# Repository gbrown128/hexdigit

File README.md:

# hexdigit
A 4-bit hex seven-segment display decoder.

Hex decoding by default, with blanking signal and an option to force decimal
display only.

Once the hardware is made, a range of additional features are planned, taking
advantage of the daisy chaining feature using UART.

# Hardware

The above render shows the basic goal of the product - to
fit entirley in the space of the seven-segment display, and
also have a DIP footprint for breadboarding.

The harware is based on an ATTiny1634, which has a whole 
host of capacity for future expansion.

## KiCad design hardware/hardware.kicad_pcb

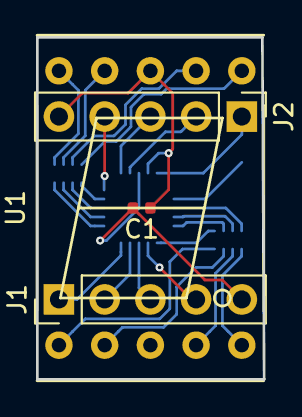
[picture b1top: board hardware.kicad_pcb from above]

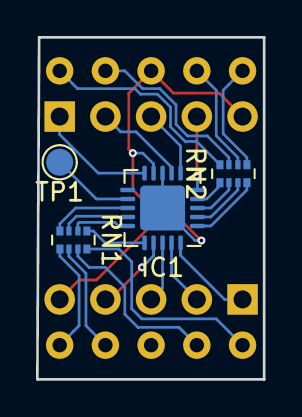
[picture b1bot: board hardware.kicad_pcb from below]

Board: 2 copper layers, 12.6 x 19.0 mm, 8 parts (4 on the bottom side), 27 nets.

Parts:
C1: 1u; C_0402_1005Metric
IC1: ATTINY1634-MU; QFN-20-1EP_4x4mm_P0.5mm_EP2.5x2.5mm
J1, J2: Conn_01x05_Male; PinHeader_1x05_P2.54mm_Vertical
RN1, RN2: 150; R_Array_Convex_4x0402
TP1: ~RESET; TestPoint_Pad_D1.5mm
U1: KCSA02-105; 7SegmentLED_LTS6760_LTS6780

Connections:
+5V: C1.1, IC1.9, J2.5, U1.8
/DA: RN2.7, U1.7
/DB: RN2.8, U1.6
/DC: RN1.6, U1.4
/DD: RN1.7, U1.2
/DDP: RN1.5, U1.5
/DE: RN1.8, U1.1
/DF: RN2.6, U1.9
/DG: RN2.5, U1.10
/~RESET: IC1.12, TP1.1
D0: IC1.5, J2.4
D1: IC1.6, J2.3
D2: IC1.7, J2.2
D3: IC1.10, J2.1
DC_I: IC1.18, J1.3
DC_O: IC1.19, J1.2
DEC: IC1.17, J1.4
EN: IC1.20, J1.1
GND: C1.2, IC1.8, IC1.21, J1.5
~DP: IC1.4, RN2.1
~SEG_A: IC1.14, RN1.3
~SEG_B: IC1.13, RN1.4
~SEG_C: IC1.3, RN2.2
~SEG_D: IC1.2, RN2.3
~SEG_E: IC1.1, RN2.4
~SEG_F: IC1.15, RN1.2
~SEG_G: IC1.16, RN1.1

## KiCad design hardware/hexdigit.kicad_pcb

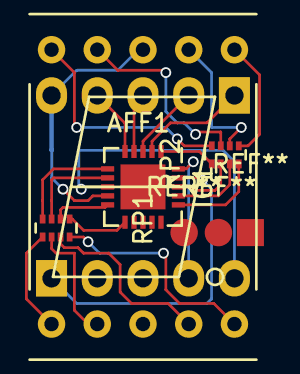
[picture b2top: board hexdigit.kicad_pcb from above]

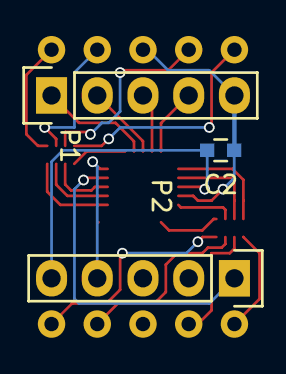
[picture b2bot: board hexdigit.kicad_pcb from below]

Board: 2 copper layers, 7 parts (3 on the bottom side), 24 nets.

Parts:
AFF1: 7SEGMENTS; 7SegmentLED_LTS6760_LTS6780
C2: 100n; C_0603
IC1: ATTINY1634-MU; QFN-20-1EP_4x4mm_Pitch0.5mm
P1, P2: CONN_01X05; Pin_Header_Straight_1x05
RP1, RP2: 330; R_Array_Concave_4x0402

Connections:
+5V: AFF1.3, AFF1.8, C2.1, IC1.9, P1.5
D0: IC1.2, P1.1
D1: IC1.3, P1.2
D2: IC1.4, P1.3
D3: IC1.5, P1.4
DC_IN: IC1.20, P2.4
DC_OUT: IC1.19, P2.1
DIG_A: IC1.17, RP2.7
DIG_B: IC1.16, RP2.8
DIG_C: IC1.10, RP1.6
DIG_D: IC1.7, RP1.7
DIG_E: IC1.6, RP1.8
DIG_F: IC1.18, RP2.6
DIG_G: IC1.1, RP2.5
DP: IC1.11, RP1.5
GND: C2.2, IC1.8, P2.5
unnamed: AFF1.1, RP1.1
unnamed: AFF1.2, RP1.2
unnamed: AFF1.4, RP1.3
unnamed: AFF1.5, RP1.4
unnamed: AFF1.6, RP2.1
unnamed: AFF1.7, RP2.2
unnamed: AFF1.9, RP2.3
unnamed: AFF1.10, RP2.4

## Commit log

2017-05-08 + Initial revision of schematic.
2017-05-08 * Changed schematic to make PCB tidier + Add initial rev of PCB
2017-05-16 * Tweaks
2017-05-16 * Redid the hardware to ensure DRC rules were correctly configured. * This version was sent out for check by the board house.
2017-05-16 + 3D Renders + Polished up the readme.
2017-05-16 + BOM for first hardware run.
2017-05-16 + Add a 1uF decoupling capacitor to the power rails.
2017-05-17 + Add the gerbers sent out for the first prototype run.
2017-05-30 + Add the display font.
2017-05-30 + Full font set sweep as a sanity check. A mess because my micro has a broken PORTC!
2017-05-30 + Now using the correct pin numbers - port D replaces port C on the atmega644p I'm using for programming because it's PORTC has some blown IO!
2017-08-14 + Add Doxygen setup, commented the font file to play around with comment layout. * Some minor changes to the PCB, need to sanity check this commit (project has been a bit stagnant the past few months!
2017-08-14 + A few notes on the way communications will work. + 3D renders for the readme.
2017-12-19 + Add source code, and a few test files.
2017-12-19 * Clear out an old binary, move the non-source test.c
2017-12-21 + Implement display functions.
2017-12-21 * Tidy up, tweaks, etc.
2017-12-21 + Add an 'i' character as just segment C. Kinda works. + Add a string print mode. Not the best but it does work.
2018-08-29 + Add a hexidecimal display function. + Add initialisation for the ADC.
2018-08-29 * Redo layout to bring components to the bottom of the board. ** Note this has changed the device pinout somewhat! * Bring everything into kicad 5 + Add kicad ignores.
